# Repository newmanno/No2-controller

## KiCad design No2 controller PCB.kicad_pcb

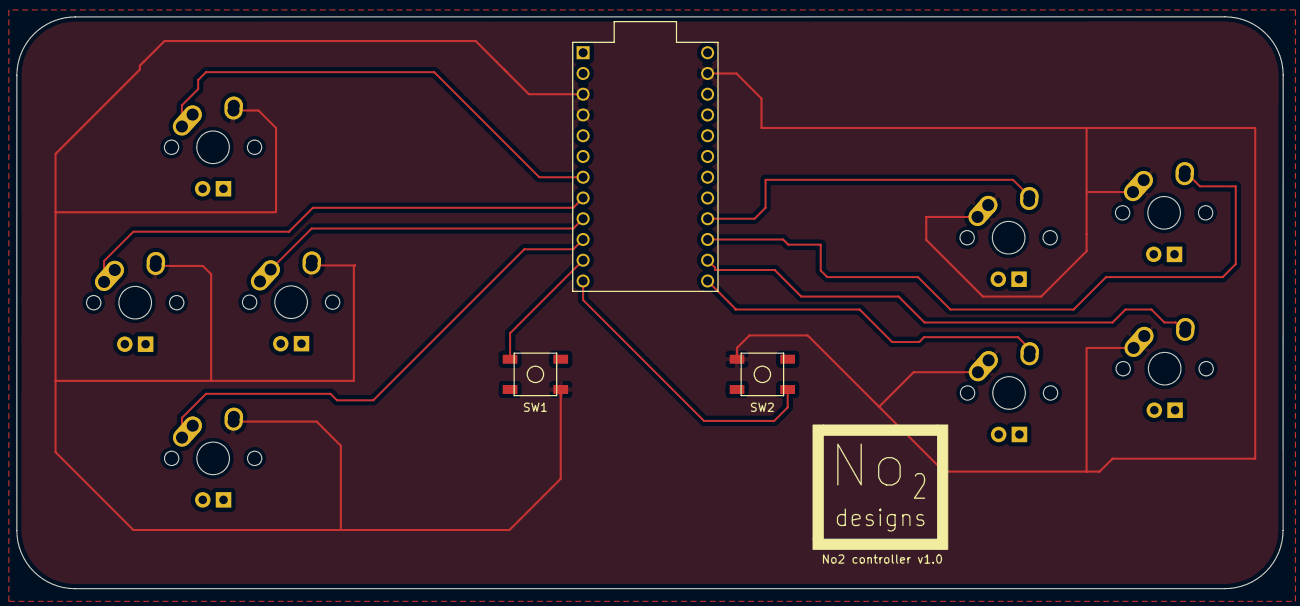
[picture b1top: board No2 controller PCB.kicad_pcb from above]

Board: 2 copper layers, 155.0 x 70.0 mm, 11 parts (0 on the bottom side), 11 nets.

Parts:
MX1, MX2, MX3, MX4, MX5, MX6, MX7, MX8: MX-NoLED; MX-1U
SW1, SW2: SW_Push; SKQG-1155865
U1: ProMicro

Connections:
GND: MX1.2, MX2.2, MX3.2, MX4.2, MX5.1, MX6.1, MX7.1, MX8.1, SW1.1, SW2.2, U1.3, U1.4, U1.23
unnamed: MX1.1, U1.8
unnamed: MX2.1, U1.7
unnamed: MX3.1, U1.10
unnamed: MX4.1, U1.9
unnamed: MX5.2, U1.16
unnamed: MX6.2, U1.13
unnamed: MX7.2, U1.15
unnamed: MX8.2, U1.14
unnamed: SW1.2, U1.11
unnamed: SW2.1, U1.12

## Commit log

2022-05-25 Initialize project
2022-05-25 Add submodules
2022-05-25 Create fp-lib-table
2022-05-25 Update fp-lib-table
2022-05-25 Add pro micro submodule
2022-05-26 added schematic
2022-05-26 PCB traces done
2022-05-26 completed design
2022-05-26 Gerbers created
2022-05-26 Minor changes
2022-05-27 added silkscreen, submitted to JLC
2022-05-29 QMK files
